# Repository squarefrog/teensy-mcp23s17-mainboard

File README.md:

# teensy-mcp23s17-mainboard
A breakout PCB for linking the Teensy 3.2 with 3x MCP23S17 SOIC packages.

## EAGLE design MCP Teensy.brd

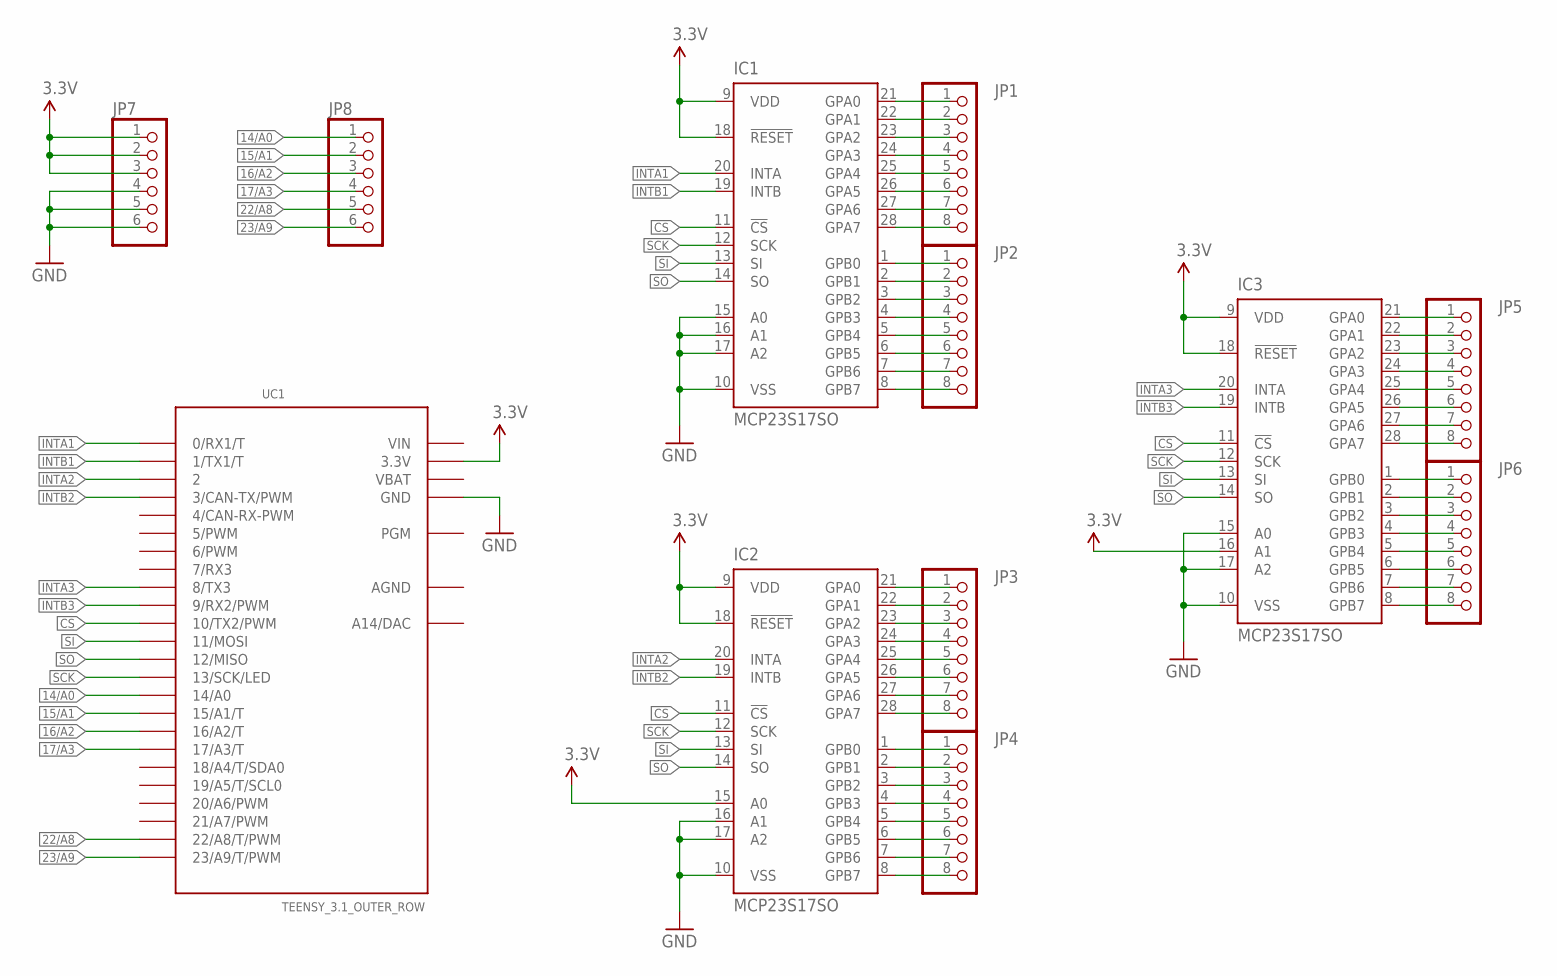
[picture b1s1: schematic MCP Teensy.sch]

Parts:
IC1, IC2, IC3: MCP23S17SO; SO28W
JP1, JP2, JP3, JP4, JP5, JP6: PINHD-1X8LOCK; 1X08-LOCK
JP7, JP8: PINHD-1X6LOCK; 1X06-BIGLOCK
UC1: TEENSY_3.1_OUTER_ROW; TEENSY3-OUTER_ROW

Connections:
3.3V: IC1.9 (VDD), IC1.18 (!RESET), IC2.9 (VDD), IC2.15 (A0), IC2.18 (!RESET), IC3.9 (VDD), IC3.16 (A1), IC3.18 (!RESET), JP7.1, JP7.2, JP7.3, UC1.3.3V, UC1.3.3V1 (3.3V)
14/A0: JP8.1, UC1.14/A0
15/A1: JP8.2, UC1.15/A1 (15/A1/T)
16/A2: JP8.3, UC1.16/A2 (16/A2/T)
17/A3: JP8.4, UC1.17/A3 (17/A3/T)
22/A8: JP8.5, UC1.22/A8 (22/A8/T/PWM)
23/A9: JP8.6, UC1.23/A9 (23/A9/T/PWM)
AGND: UC1.AGND
CS: IC1.11 (!CS), IC2.11 (!CS), IC3.11 (!CS), UC1.10 (10/TX2/PWM)
GND: IC1.10 (VSS), IC1.15 (A0), IC1.16 (A1), IC1.17 (A2), IC2.10 (VSS), IC2.16 (A1), IC2.17 (A2), IC3.10 (VSS), IC3.15 (A0), IC3.17 (A2), JP7.4, JP7.5, JP7.6, UC1.GND, UC1.GND1 (GND)
INTA1: IC1.20 (INTA), UC1.0 (0/RX1/T)
INTA2: IC2.20 (INTA), UC1.2
INTA3: IC3.20 (INTA), UC1.8 (8/TX3)
INTB1: IC1.19 (INTB), UC1.1 (1/TX1/T)
INTB2: IC2.19 (INTB), UC1.3 (3/CAN-TX/PWM)
INTB3: IC3.19 (INTB), UC1.9 (9/RX2/PWM)
unnamed: IC1.21 (GPA0), JP1.1
unnamed: IC1.22 (GPA1), JP1.2
unnamed: IC1.23 (GPA2), JP1.3
unnamed: IC1.24 (GPA3), JP1.4
unnamed: IC1.25 (GPA4), JP1.5
unnamed: IC1.26 (GPA5), JP1.6
unnamed: IC1.27 (GPA6), JP1.7
unnamed: IC1.28 (GPA7), JP1.8
unnamed: IC1.1 (GPB0), JP2.1
unnamed: IC1.2 (GPB1), JP2.2
unnamed: IC1.3 (GPB2), JP2.3
unnamed: IC1.4 (GPB3), JP2.4
unnamed: IC1.5 (GPB4), JP2.5
unnamed: IC1.6 (GPB5), JP2.6
unnamed: IC1.7 (GPB6), JP2.7
unnamed: IC1.8 (GPB7), JP2.8
unnamed: IC2.21 (GPA0), JP3.1
unnamed: IC2.22 (GPA1), JP3.2
unnamed: IC2.23 (GPA2), JP3.3
unnamed: IC2.24 (GPA3), JP3.4
unnamed: IC2.25 (GPA4), JP3.5
unnamed: IC2.26 (GPA5), JP3.6
unnamed: IC2.27 (GPA6), JP3.7
unnamed: IC2.28 (GPA7), JP3.8
unnamed: IC2.1 (GPB0), JP4.1
unnamed: IC2.2 (GPB1), JP4.2
unnamed: IC2.3 (GPB2), JP4.3
unnamed: IC2.4 (GPB3), JP4.4
unnamed: IC2.5 (GPB4), JP4.5
unnamed: IC2.6 (GPB5), JP4.6
unnamed: IC2.7 (GPB6), JP4.7
unnamed: IC2.8 (GPB7), JP4.8
unnamed: IC3.21 (GPA0), JP5.1
unnamed: IC3.22 (GPA1), JP5.2
unnamed: IC3.23 (GPA2), JP5.3
unnamed: IC3.24 (GPA3), JP5.4
unnamed: IC3.25 (GPA4), JP5.5
unnamed: IC3.26 (GPA5), JP5.6
unnamed: IC3.27 (GPA6), JP5.7
unnamed: IC3.28 (GPA7), JP5.8
unnamed: IC3.1 (GPB0), JP6.1
unnamed: IC3.2 (GPB1), JP6.2
unnamed: IC3.3 (GPB2), JP6.3
unnamed: IC3.4 (GPB3), JP6.4
unnamed: IC3.5 (GPB4), JP6.5
unnamed: IC3.6 (GPB5), JP6.6
unnamed: IC3.7 (GPB6), JP6.7
unnamed: IC3.8 (GPB7), JP6.8
SCK: IC1.12 (SCK), IC2.12 (SCK), IC3.12 (SCK), UC1.13 (13/SCK/LED)
SI: IC1.13 (SI), IC2.13 (SI), IC3.13 (SI), UC1.11 (11/MOSI)
SO: IC1.14 (SO), IC2.14 (SO), IC3.14 (SO), UC1.12 (12/MISO)
VBAT: UC1.VBAT
VIN: UC1.VIN

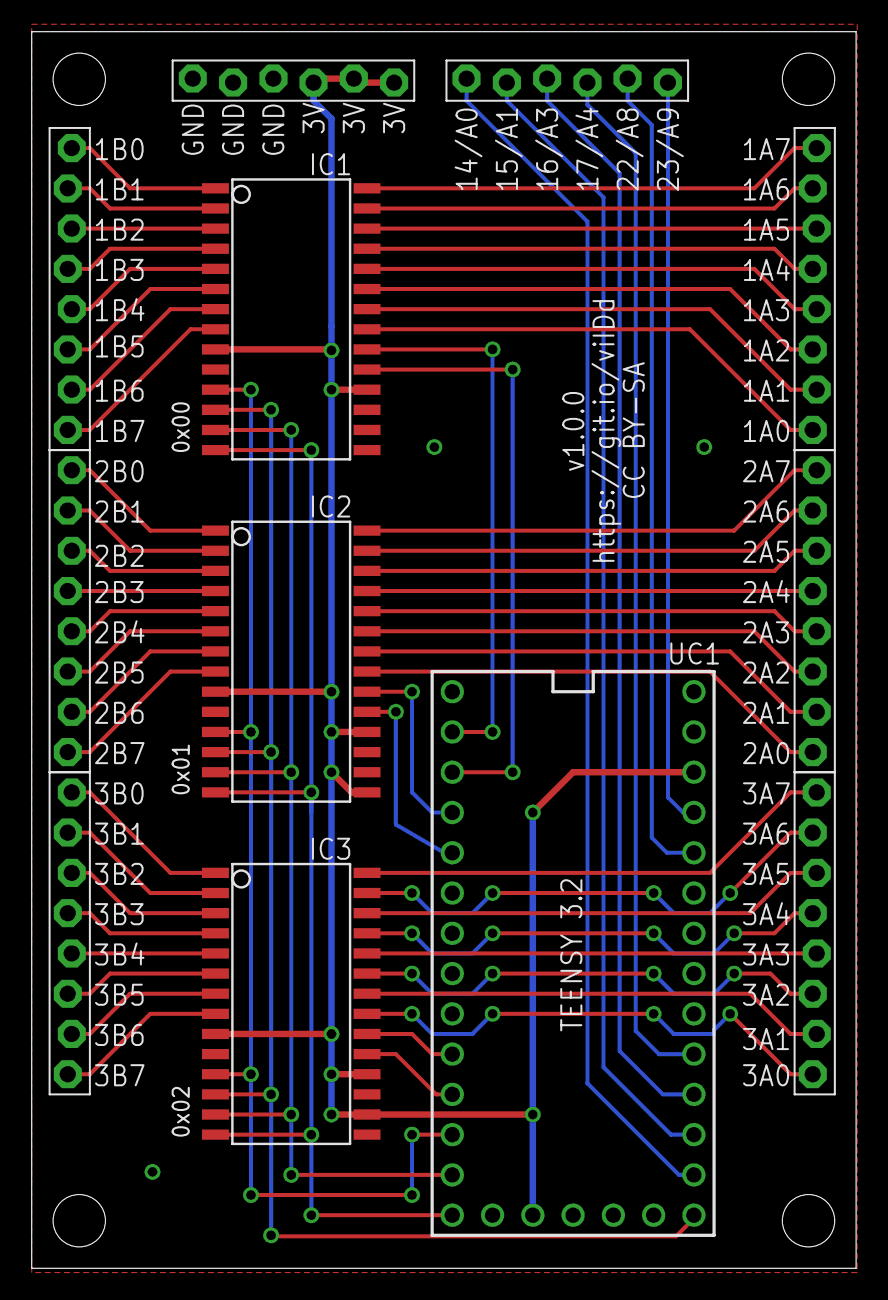
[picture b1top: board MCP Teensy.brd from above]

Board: 2 copper layers, 52.0 x 78.0 mm, 16 parts (0 on the bottom side), 66 nets.

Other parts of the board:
U$2, U$3, U$4, U$5: STAND-OFF

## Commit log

2016-09-01 Add gitignore
2016-09-01 Add board and schematic

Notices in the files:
MCP Teensy.brd:
CC BY-SA
parts and their libraries:
SparkFun-Electromechanical: Licensing: Creative Commons ShareAlike 4.0 International - https://creativecommons.org/licenses/by-sa/4.0
